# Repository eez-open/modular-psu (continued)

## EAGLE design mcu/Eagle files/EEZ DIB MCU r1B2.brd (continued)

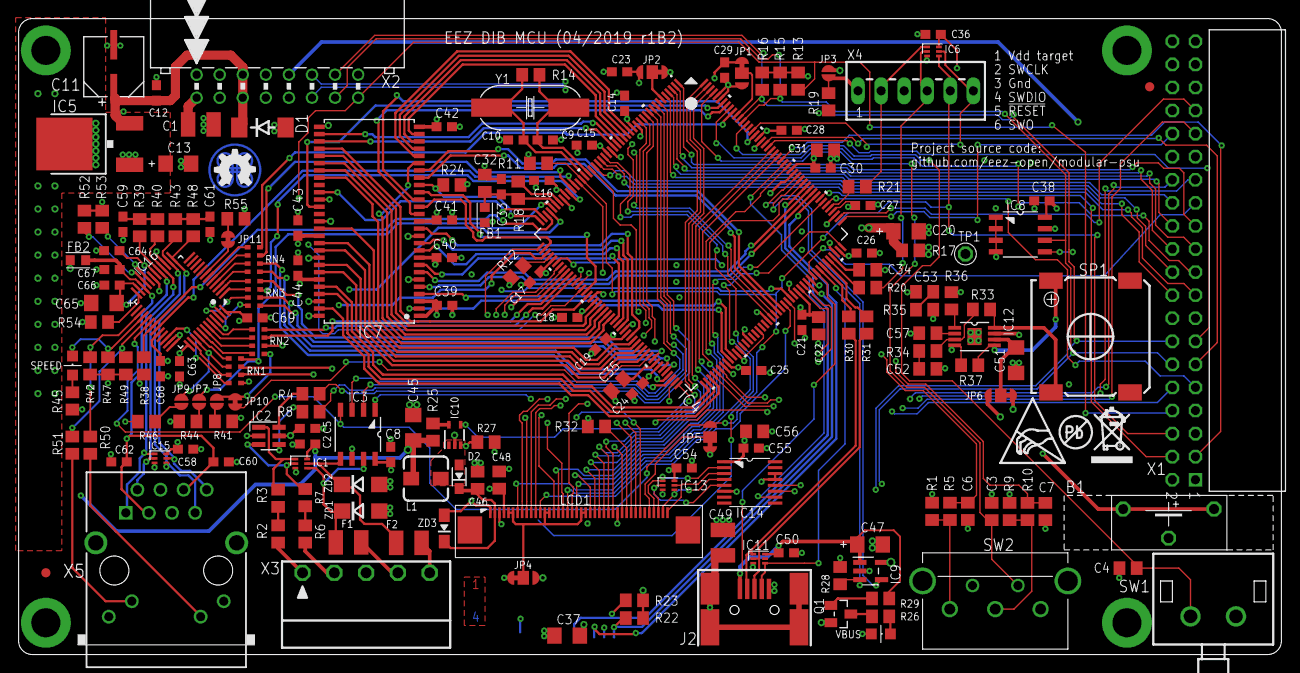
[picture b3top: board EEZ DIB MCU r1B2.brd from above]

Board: 4 copper layers, 139.0 x 70.0 mm, 188 parts (1 on the bottom side), 228 nets.

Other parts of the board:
EEZ_SIGNATURE: SIGNATURESMALL; SIGNATURE_5MM
U$1: RECYCLE_BIN1/8
U$5: PB_SMALL
U$6: ESD_SYMBOL
